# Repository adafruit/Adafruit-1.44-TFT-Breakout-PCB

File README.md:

## Adafruit 1.44" TFT LCD Color Display Breakout PCB

<a href="http://www.adafruit.com/products/2088"><br/>
Click here to purchase one from the Adafruit shop</a>

PCB files for the Adafruit 1.44 TFT Breakout. Format is EagleCAD schematic and board layout
* https://www.adafruit.com/products/2088

### Description

This lovely little display breakout is the best way to add a small, colorful and bright display to any project. Since the display uses 4-wire SPI to communicate and has its own pixel-addressable frame buffer, it can be used with every kind of microcontroller. Even a very small one with low memory and few pins available!

The 1.44" display has 128x128 color pixels. Unlike the low cost "Nokia 6110" and similar LCD displays, which are CSTN type and thus have poor color and slow refresh, this display is a true TFT! The TFT driver (ST7735R) can display full 16-bit color using our library code.

The breakout has the TFT display soldered on (it uses a delicate flex-circuit connector) as well as a ultra-low-dropout 3.3V regulator and a 3/5V level shifter so you can use it with 3.3V or 5V power and logic. We also had a little space so we placed a microSD card holder so you can easily load full color bitmaps from a FAT16/FAT32 formatted microSD card. The microSD card is not included.

NEW! As of February 28, 2023 - we've updated this TFT breakout with an EYESPI connector to make cabling easier with an 18-pin FPC. We also used Adafruit Pinguin to make a lovely silkscreen. The board is otherwise the same size, pinout, and functionality.

### License

Adafruit invests time and resources providing this open source design, please support Adafruit and open-source hardware by purchasing products from [Adafruit](https://www.adafruit.com)!

Designed by Limor Fried/Ladyada for Adafruit Industries.

Creative Commons Attribution/Share-Alike, all text above must be included in any redistribution. See license.txt for additional details.

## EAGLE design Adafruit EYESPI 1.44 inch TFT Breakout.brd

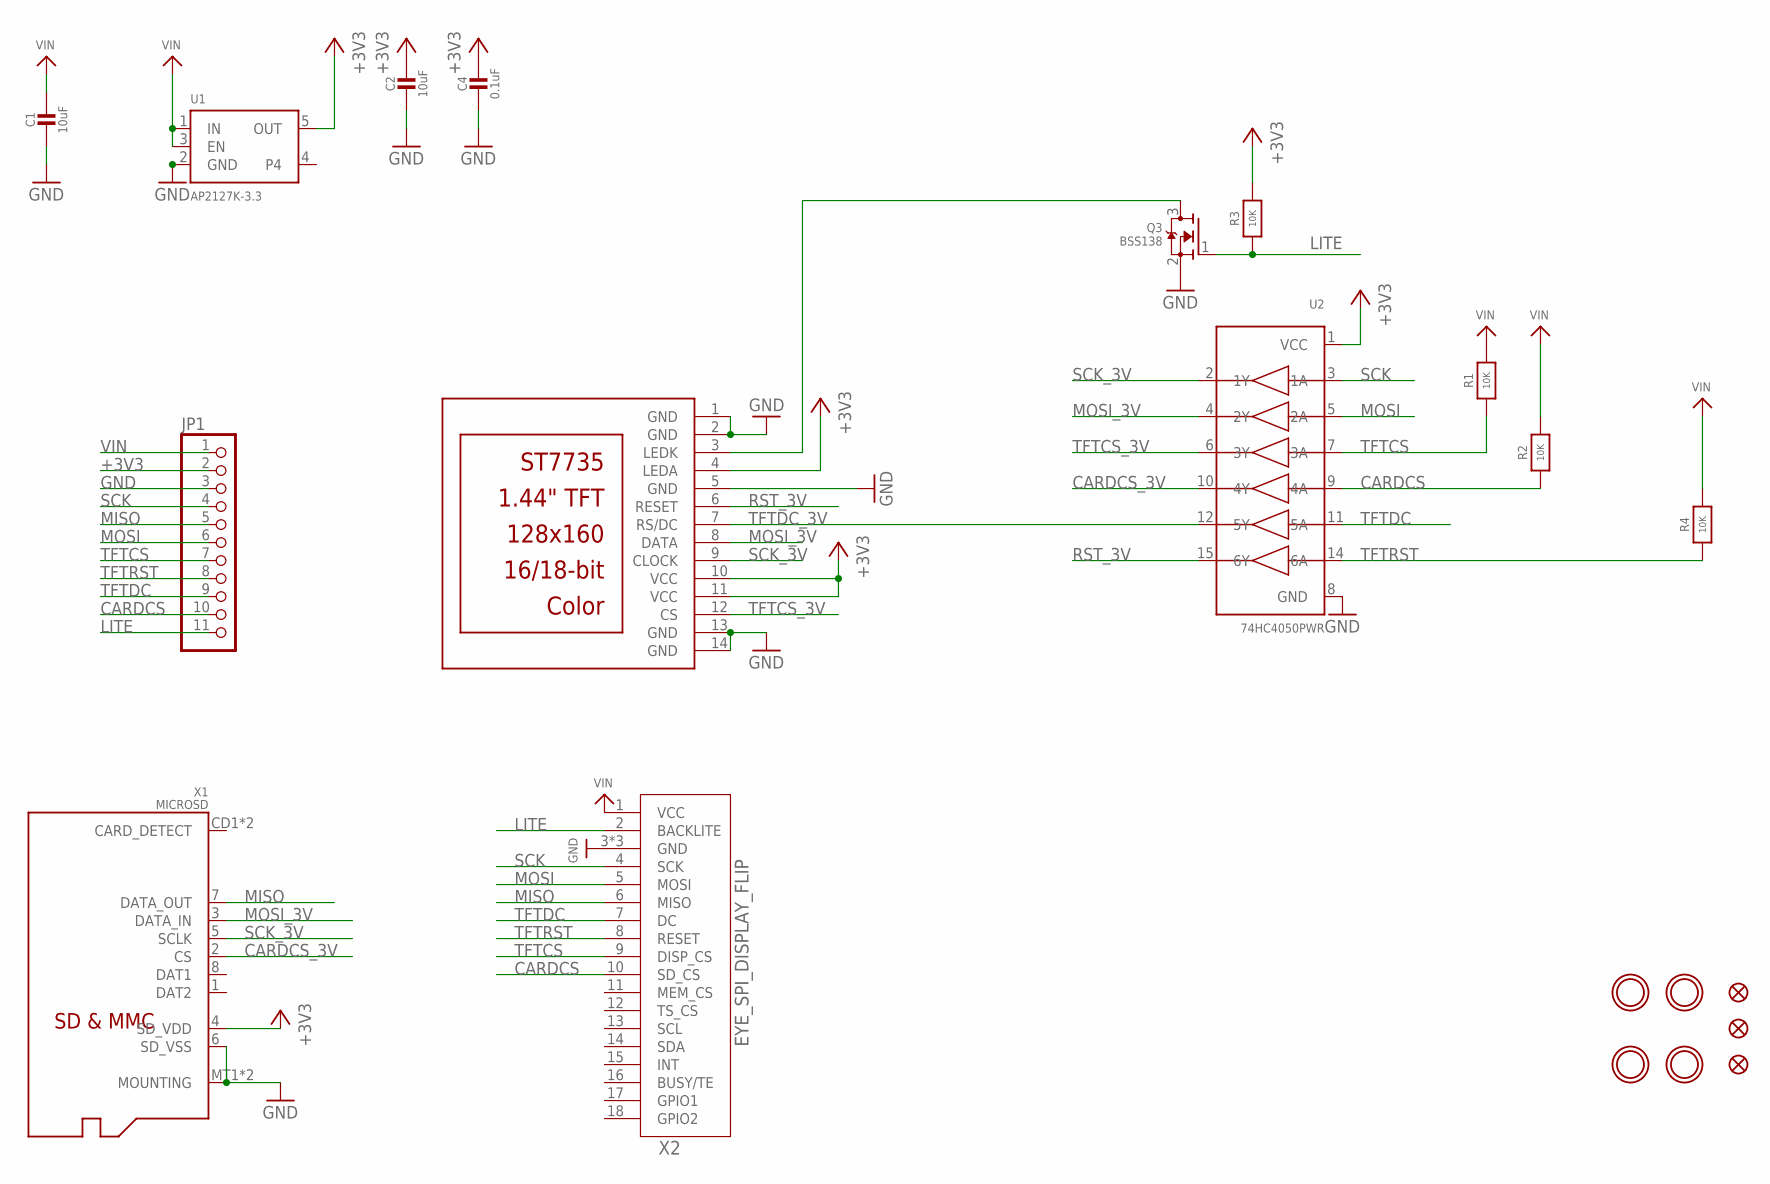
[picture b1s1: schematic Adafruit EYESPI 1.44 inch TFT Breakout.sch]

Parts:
C1, C2: 10uF; 0805-NO
C4: 0.1uF; 0603-NO
JP1: HEADER-1X1176MIL; 1X11_ROUND_76
Q3: BSS138; SOT23-WIDE
R1, R2, R3, R4: 10K; 0603-NO
TFT2: DISP_LCD_ST7735_1.44IN; TFT_1.44IN_128_128
U1: AP2127K-3.3; SOT23-5
U2: 74HC4050PWR; TSSOP16
U$3, U$4, U$5: FIDUCIAL_1MM
U$7, U$8, U$9, U$10: MOUNTINGHOLE2.5; MOUNTINGHOLE_2.5_PLATED
X1: MICROSD
X2: EYE_SPI_DISPLAY_FLIP; EYE_SPI_DISPLAY_BOTCONTACT

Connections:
+3V3: C2.1, C4.1, JP1.2, R3.2, TFT2.4 (LEDA), TFT2.10 (VCC), TFT2.11 (VCC), U1.5 (OUT), U2.1 (VCC), X1.4 (SD_VDD)
CARDCS: JP1.10, R2.1, U2.9 (4A), X2.10 (SD_CS)
CARDCS_3V: U2.10 (4Y), X1.2 (CS)
GND: C1.2, C2.2, C4.2, JP1.3, Q3.2 (S), TFT2.1 (GND), TFT2.2 (GND), TFT2.5 (GND), TFT2.13 (GND), TFT2.14 (GND), U1.2 (GND), U2.8 (GND), X1.6 (SD_VSS), X1.MT1 (MOUNTING), X1.MT2 (MOUNTING), X2.3 (GND), X2.SUPPORT1 (GND), X2.SUPPORT2 (GND)
LITE: JP1.11, Q3.1 (G), R3.1, X2.2 (BACKLITE)
MISO: JP1.5, X1.7 (DATA_OUT), X2.6 (MISO)
MOSI: JP1.6, U2.5 (2A), X2.5 (MOSI)
MOSI_3V: TFT2.8 (DATA), U2.4 (2Y), X1.3 (DATA_IN)
unnamed: Q3.3 (D), TFT2.3 (LEDK)
RST_3V: TFT2.6 (RESET), U2.15 (6Y)
SCK: JP1.4, U2.3 (1A), X2.4 (SCK)
SCK_3V: TFT2.9 (CLOCK), U2.2 (1Y), X1.5 (SCLK)
TFTCS: JP1.7, R1.1, U2.7 (3A), X2.9 (DISP_CS)
TFTCS_3V: TFT2.12 (CS), U2.6 (3Y)
TFTDC: JP1.9, U2.11 (5A), X2.7 (DC)
TFTDC_3V: TFT2.7 (RS/DC), U2.12 (5Y)
TFTRST: JP1.8, R4.1, U2.14 (6A), X2.8 (RESET)
VIN: C1.1, JP1.1, R1.2, R2.2, R4.2, U1.1 (IN), U1.3 (EN), X2.1 (VCC)

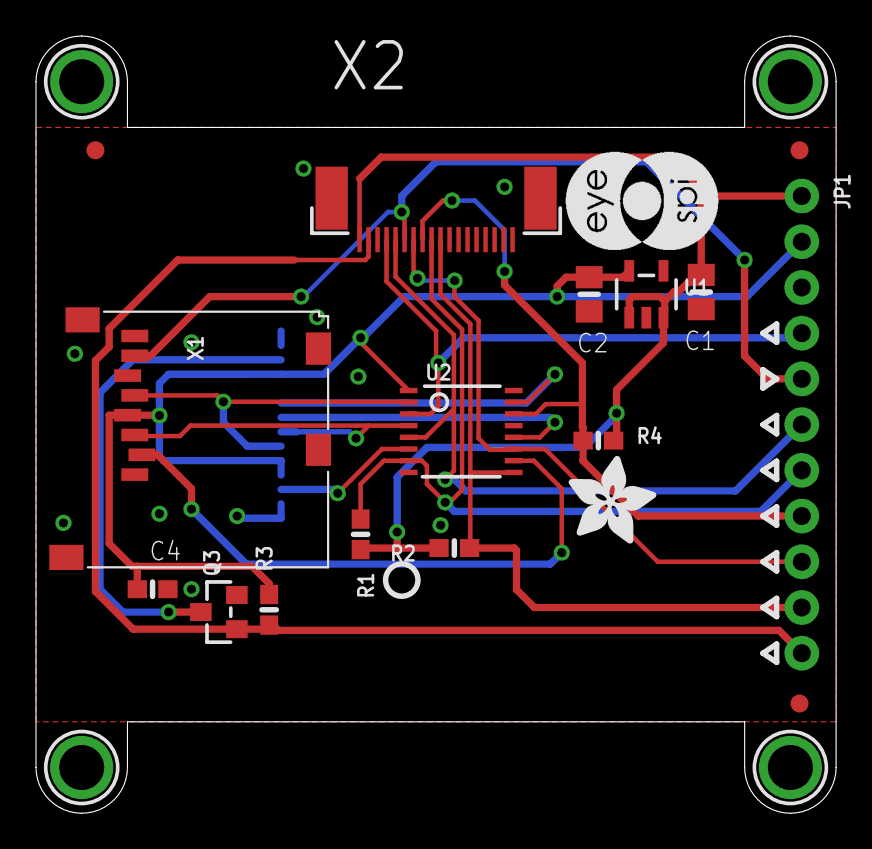
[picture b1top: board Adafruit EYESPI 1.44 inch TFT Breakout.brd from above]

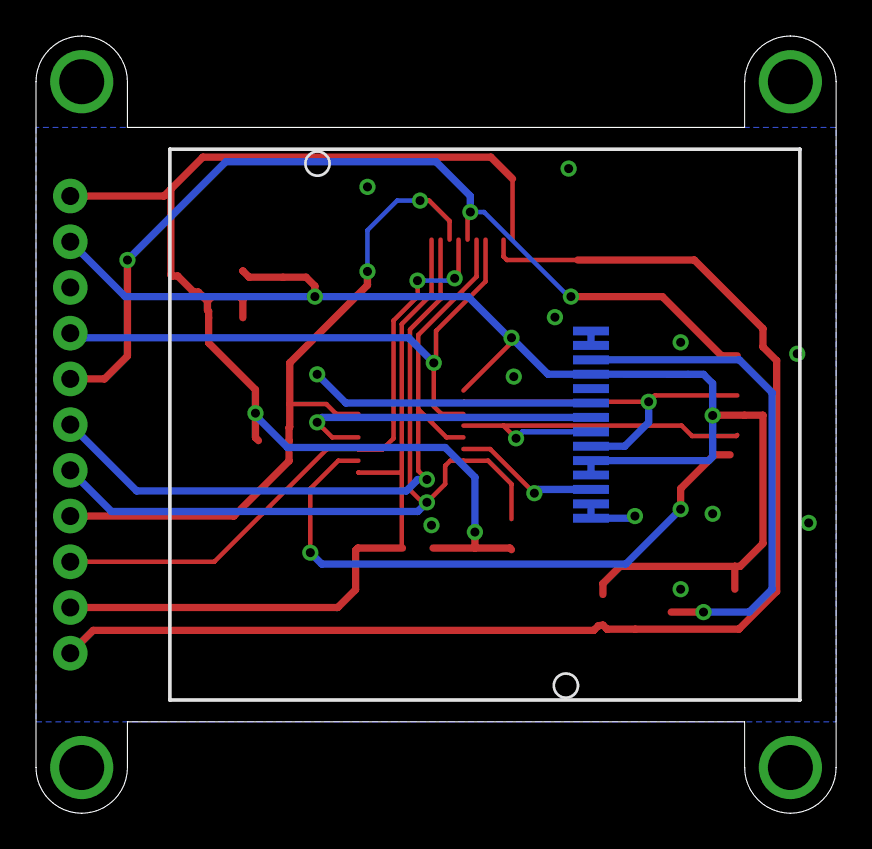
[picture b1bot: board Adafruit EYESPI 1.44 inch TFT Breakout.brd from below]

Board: 2 copper layers, 44.5 x 43.2 mm, 51 parts (12 on the bottom side), 18 nets.

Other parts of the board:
PLABEL0: PLABEL0
PLABEL1: PLABEL1
PLABEL2: PLABEL2
PLABEL3: PLABEL3
PLABEL4: PLABEL4
PLABEL5: PLABEL5
PLABEL6: PLABEL6
PLABEL7: PLABEL7
PLABEL8: PLABEL8
PLABEL9: PLABEL9
PLABEL10: PLABEL10
PLABEL11: PLABEL11
PLABEL12: PLABEL12
PLABEL13: PLABEL13
PLABEL14: PLABEL14
PLABEL15: PLABEL15
PLABEL16: PLABEL16
PLABEL17: PLABEL17
PLABEL18: PLABEL18
PLABEL19: PLABEL19
PLABEL20: PLABEL20
PLABEL21: PLABEL21
PLABEL22: PLABEL22
PLABEL23: PLABEL23
PLABEL24: PLABEL24
PLABEL25: PLABEL25
PLABEL26: PLABEL26
U$1: ADAFRUIT_5MM
U$2: PCBFEAT-REV-040
U$17: EYESPI_MINI_LOGO

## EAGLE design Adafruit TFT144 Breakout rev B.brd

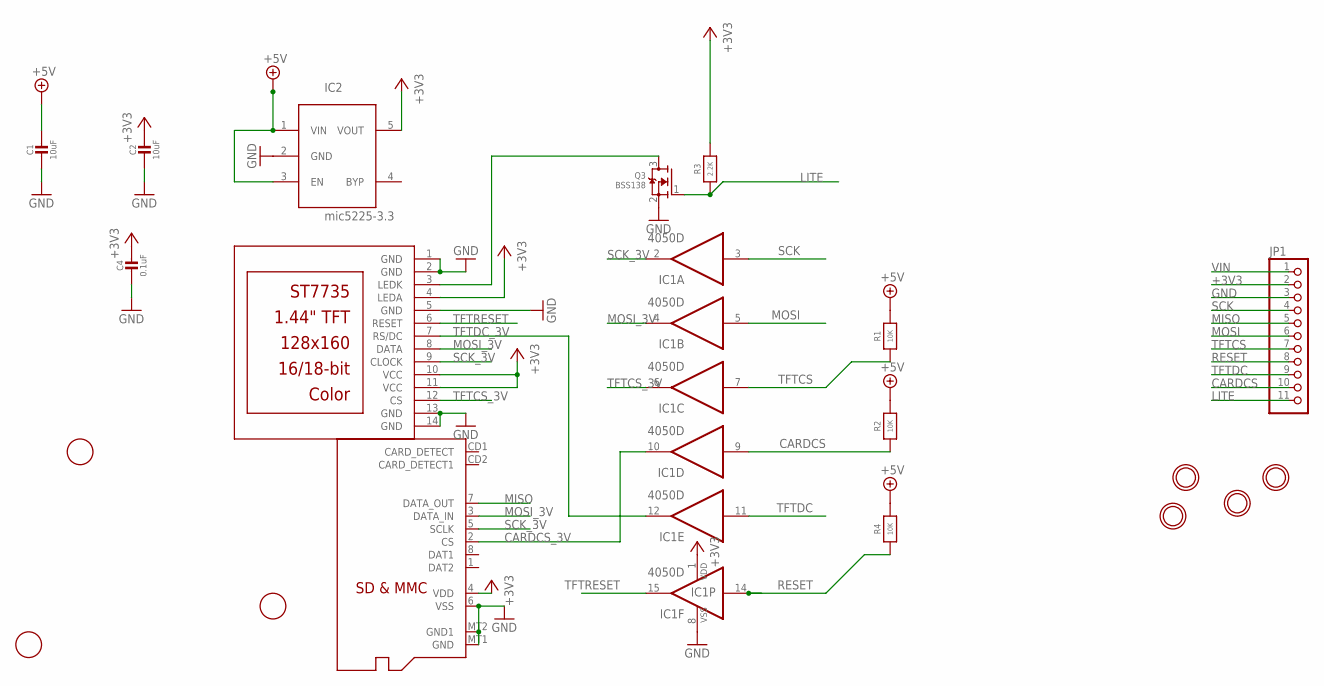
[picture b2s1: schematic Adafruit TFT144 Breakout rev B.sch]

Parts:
C1, C2: 10uF; 0805-NO
C4: 0.1uF; 0805-NO
IC1: 4050D; SO16
IC2: mic5225-3.3; SOT23-5L
JP1: HEADER-1X1176MIL; 1X11_ROUND_76
Q2: MICROSD
Q3: BSS138; SOT23-WIDE
R1, R2, R4: 10K; 0805-NO
R3: 2.2K; 0805-NO
TFT2: DISP_LCD_ST7735_1.44IN; TFT_1.44IN_128_128
U$3, U$4, U$5: FIDUCIAL; FIDUCIAL_1MM
U$7, U$8, U$9, U$10: MOUNTINGHOLE2.5; MOUNTINGHOLE_2.5_PLATED

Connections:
+3V3: C2.1, C4.1, IC1.1 (VDD), IC2.5 (VOUT), JP1.2, Q2.4 (VDD), R3.2, TFT2.4 (LEDA), TFT2.10 (VCC), TFT2.11 (VCC)
CARDCS: IC1.9 (I), JP1.10, R2.1
CARDCS_3V: IC1.10 (O), Q2.2 (CS)
GND: C1.2, C2.2, C4.2, IC1.8 (VSS), IC2.2 (GND), JP1.3, Q2.6 (VSS), Q2.MT1 (GND), Q2.MT2 (GND1), Q3.2 (S), TFT2.1 (GND), TFT2.2 (GND), TFT2.5 (GND), TFT2.13 (GND), TFT2.14 (GND)
LITE: JP1.11, Q3.1 (G), R3.1
MISO: JP1.5, Q2.7 (DATA_OUT)
MOSI: IC1.5 (I), JP1.6
MOSI_3V: IC1.4 (O), Q2.3 (DATA_IN), TFT2.8 (DATA)
unnamed: Q3.3 (D), TFT2.3 (LEDK)
RESET: IC1.14 (I), JP1.8, R4.1
SCK: IC1.3 (I), JP1.4
SCK_3V: IC1.2 (O), Q2.5 (SCLK), TFT2.9 (CLOCK)
TFTCS: IC1.7 (I), JP1.7, R1.1
TFTCS_3V: IC1.6 (O), TFT2.12 (CS)
TFTDC: IC1.11 (I), JP1.9
TFTDC_3V: IC1.12 (O), TFT2.7 (RS/DC)
TFTRESET: IC1.15 (O), TFT2.6 (RESET)
VIN: C1.1, IC2.1 (VIN), IC2.3 (EN), JP1.1, R1.2, R2.2, R4.2

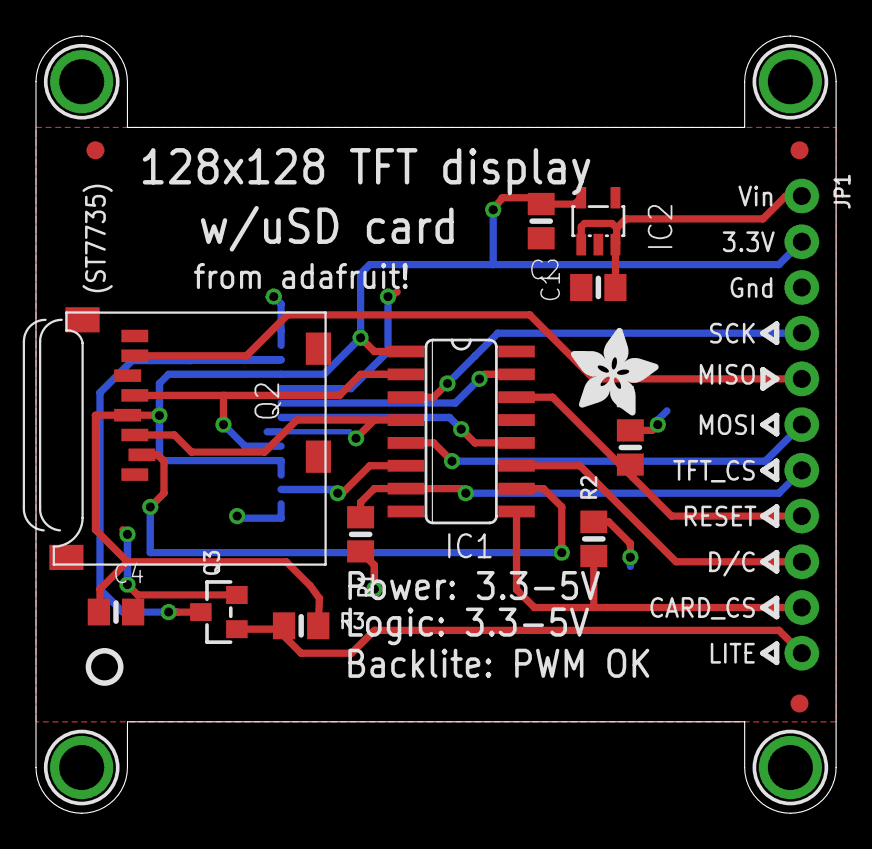
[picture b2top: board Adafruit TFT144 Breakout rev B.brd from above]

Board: 2 copper layers, 44.5 x 43.2 mm, 22 parts (1 on the bottom side), 18 nets.

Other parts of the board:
U$1: ADAFRUIT_5MM
U$2: PCBFEAT-REV-040

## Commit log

2016-04-03 init
2016-09-26 latest vers
2023-03-02 adding EYESPI files and updating readme

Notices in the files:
parts and their libraries:
microbuilder: This work is placed in the public domain, and may be freely used for commercial and non-commercial work with the following conditions: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
